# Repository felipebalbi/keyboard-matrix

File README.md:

# 4x4 Keyboard Matrix

A simple 4x4 keyboard matrix useful for testing purposes.

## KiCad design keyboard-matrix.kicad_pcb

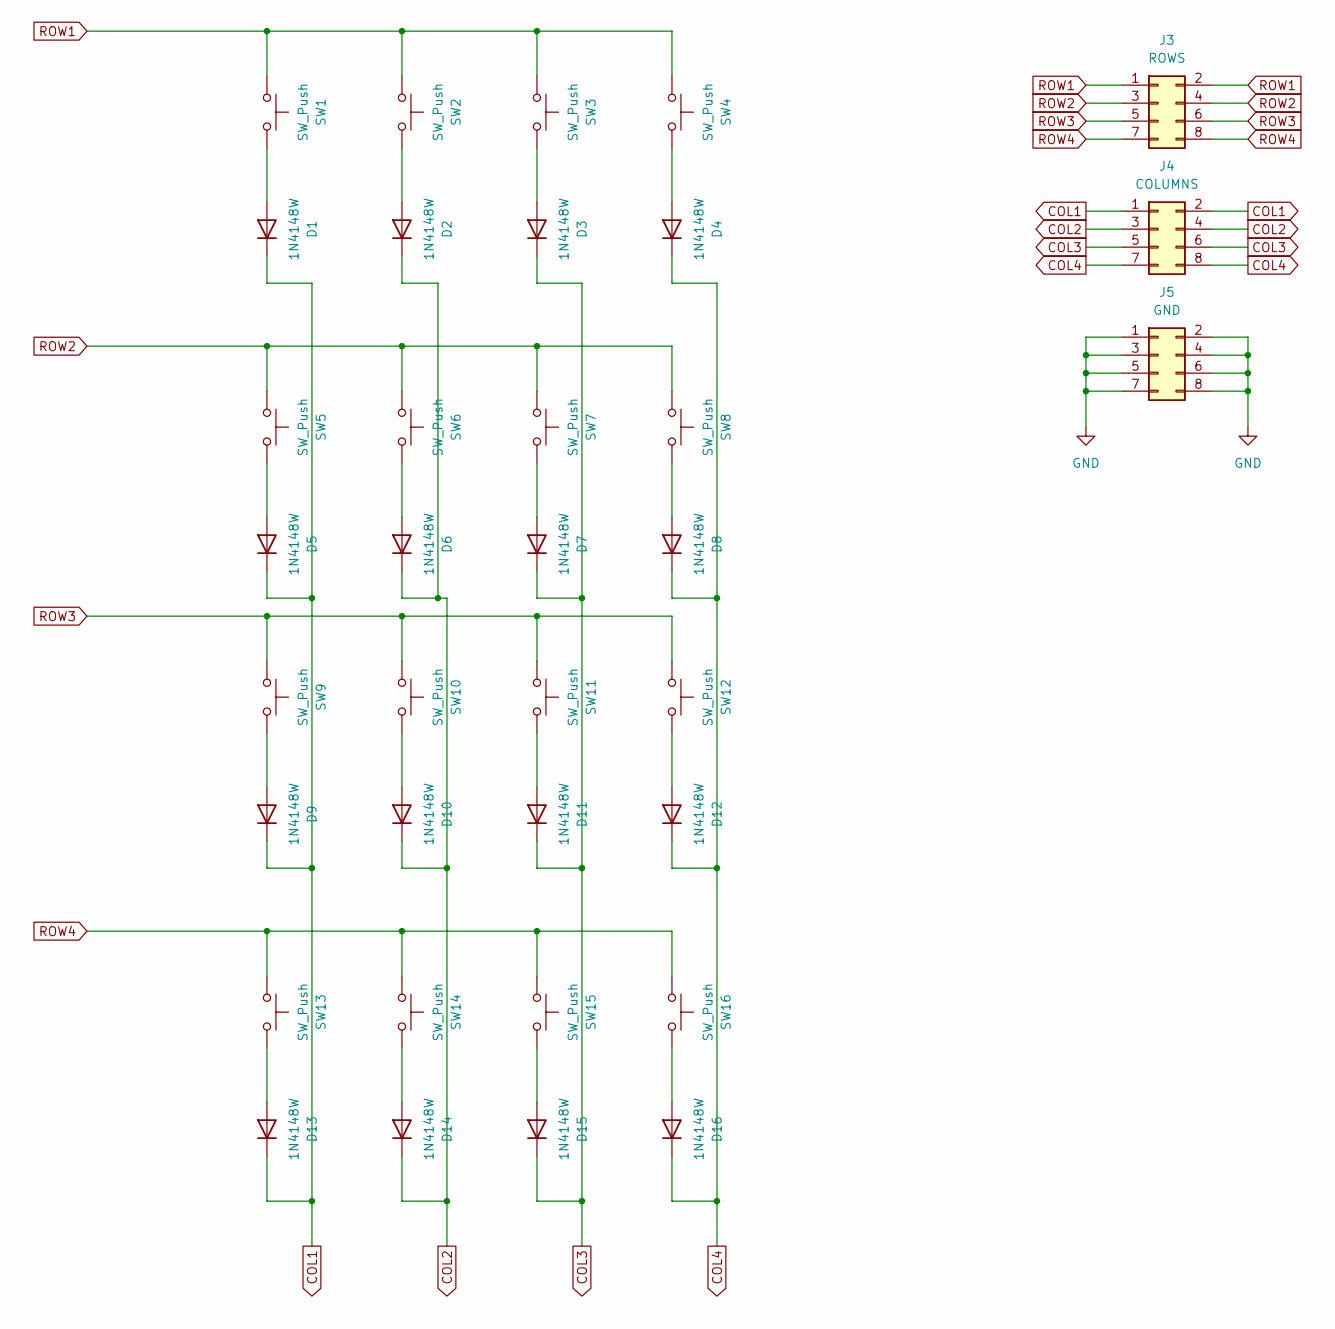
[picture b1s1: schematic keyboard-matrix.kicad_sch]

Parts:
D1, D2, D3, D4, D5, D6, D7, D8, D9, D10, D11, D12, D13, D14, D15, D16: 1N4148W; D_SOD-123
J3: ROWS; PinHeader_2x04_P2.54mm_Vertical
J4: COLUMNS; PinHeader_2x04_P2.54mm_Vertical
J5: GND; PinHeader_2x04_P2.54mm_Vertical
SW1, SW2, SW3, SW4, SW5, SW6, SW7, SW8, SW9, SW10, SW11, SW12, SW13, SW14, SW15, SW16: SW_Push; SW_PUSH_6mm

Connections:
COL1: D1.1 (K), D5.1 (K), D9.1 (K), D13.1 (K), J4.1, J4.2
COL2: D2.1 (K), D6.1 (K), D10.1 (K), D14.1 (K), J4.3, J4.4
COL3: D3.1 (K), D7.1 (K), D11.1 (K), D15.1 (K), J4.5, J4.6
COL4: D4.1 (K), D8.1 (K), D12.1 (K), D16.1 (K), J4.7, J4.8
GND: J5.1, J5.2, J5.3, J5.4, J5.5, J5.6, J5.7, J5.8
unnamed: D1.2 (A), SW1.2
unnamed: D2.2 (A), SW2.2
unnamed: D3.2 (A), SW3.2
unnamed: D4.2 (A), SW4.2
unnamed: D5.2 (A), SW5.2
unnamed: D6.2 (A), SW6.2
unnamed: D7.2 (A), SW7.2
unnamed: D8.2 (A), SW8.2
unnamed: D9.2 (A), SW9.2
unnamed: D10.2 (A), SW10.2
unnamed: D11.2 (A), SW11.2
unnamed: D12.2 (A), SW12.2
unnamed: D13.2 (A), SW13.2
unnamed: D14.2 (A), SW14.2
unnamed: D15.2 (A), SW15.2
unnamed: D16.2 (A), SW16.2
ROW1: J3.1, J3.2, SW1.1, SW2.1, SW3.1, SW4.1
ROW2: J3.3, J3.4, SW5.1, SW6.1, SW7.1, SW8.1
ROW3: J3.5, J3.6, SW9.1, SW10.1, SW11.1, SW12.1
ROW4: J3.7, J3.8, SW13.1, SW14.1, SW15.1, SW16.1

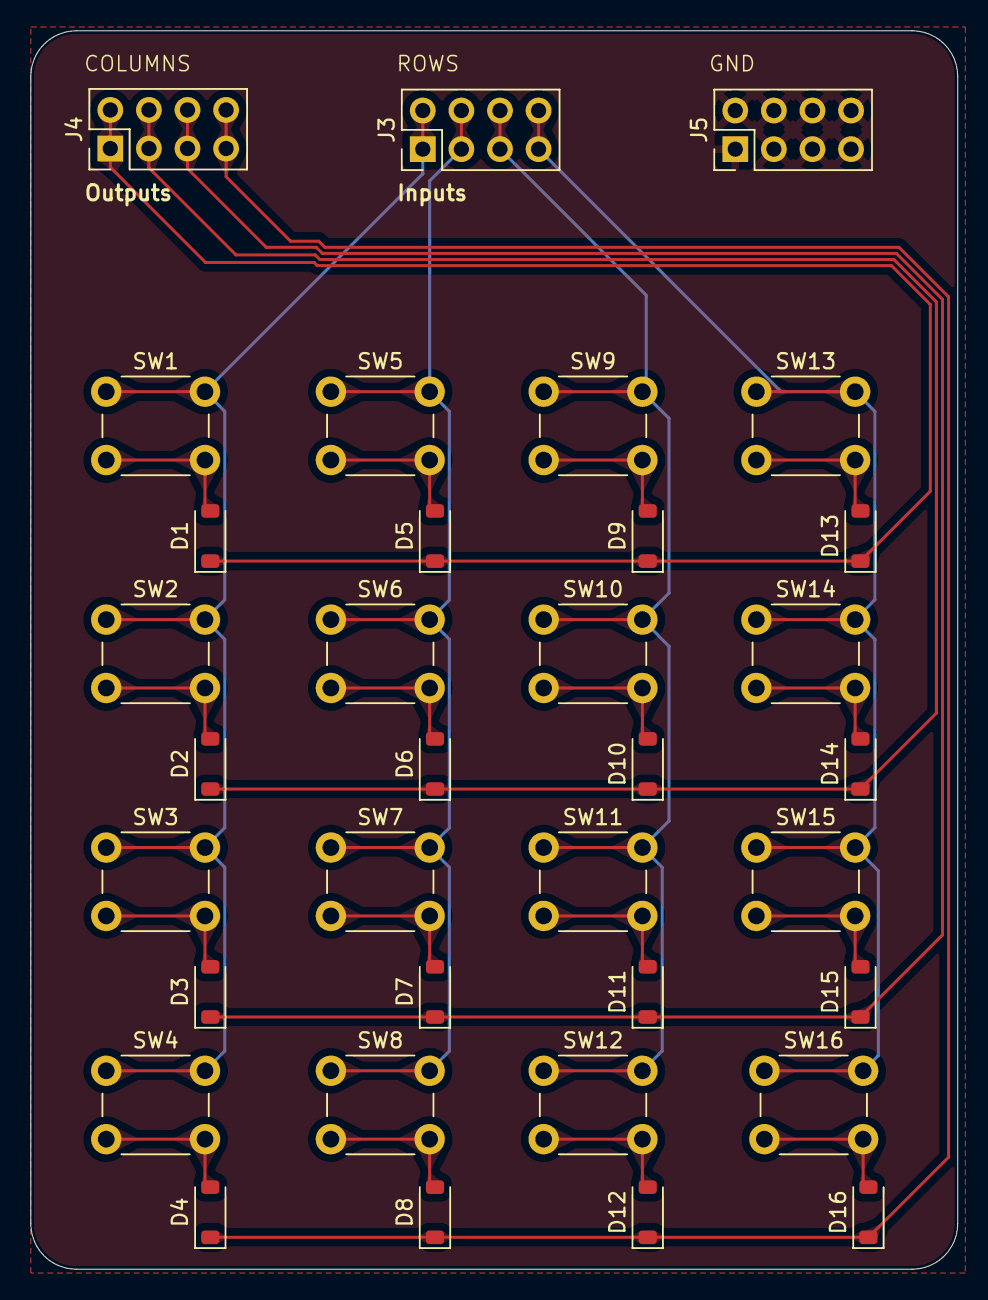
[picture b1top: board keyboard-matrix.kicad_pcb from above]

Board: 2 copper layers, 61.0 x 81.5 mm, 35 parts (0 on the bottom side), 25 nets.
